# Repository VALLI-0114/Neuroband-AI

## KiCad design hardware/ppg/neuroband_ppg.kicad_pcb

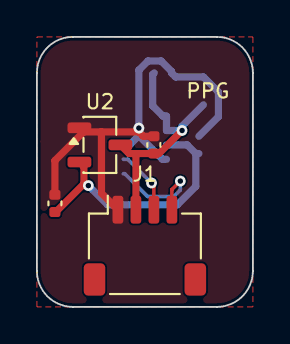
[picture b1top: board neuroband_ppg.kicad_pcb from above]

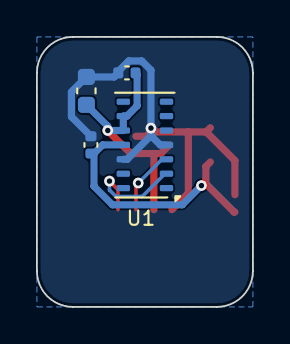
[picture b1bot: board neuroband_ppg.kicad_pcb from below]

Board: 2 copper layers, 12.0 x 15.0 mm, 8 parts (4 on the bottom side), 5 nets.

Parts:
C1, C2: 1uF; C_0402_1005Metric
C3, C5: 100nF; C_0402_1005Metric
C4: 10uF; C_0603_1608Metric
J1: MAIN; JST_SH_SM04B-SRSS-TB_1x04-1MP_P1.00mm_Horizontal
U1: MAX30102; Maxim_OLGA-14_3.3x5.6mm_P0.8mm
U2: XC6206P182MR; SOT-23-3

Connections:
1V8: C2.1, C3.1, U1.11, U2.2
3V3: C1.1, C4.1, C5.1, J1.2, U1.9, U1.10, U2.3
GND: C1.2, C2.2, C3.2, C4.2, C5.2, J1.1, U1.4, U1.12, U2.1
I2C_SCL: J1.4, U1.2
I2C_SDA: J1.3, U1.3

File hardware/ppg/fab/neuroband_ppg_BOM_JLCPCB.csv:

Comment,Designator,Footprint,LCSC Part #
1uF X5R/X7R 0402,"C1,C2",C_0402_1005Metric,
100nF X5R/X7R 0402,"C3,C5",C_0402_1005Metric,
10uF X5R/X7R 0603,C4,C_0603_1608Metric,
SM04B-SRSS-TB,J1,JST_SH_SM04B-SRSS-TB_1x04-1MP_P1.00mm_Horizontal,
MAX30102EFD+T,U1,Maxim_OLGA-14_3.3x5.6mm_P0.8mm,
XC6206P182MR,U2,SOT-23-3,

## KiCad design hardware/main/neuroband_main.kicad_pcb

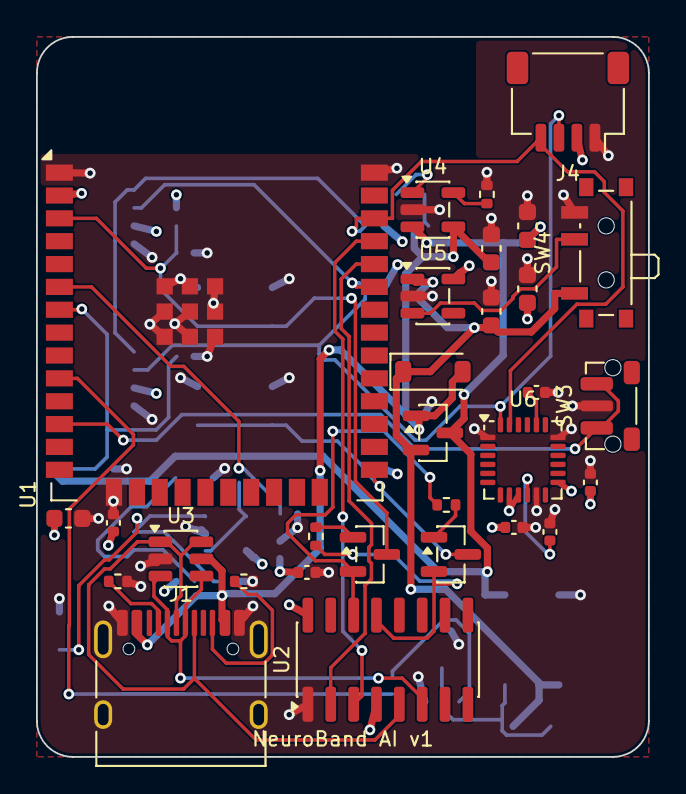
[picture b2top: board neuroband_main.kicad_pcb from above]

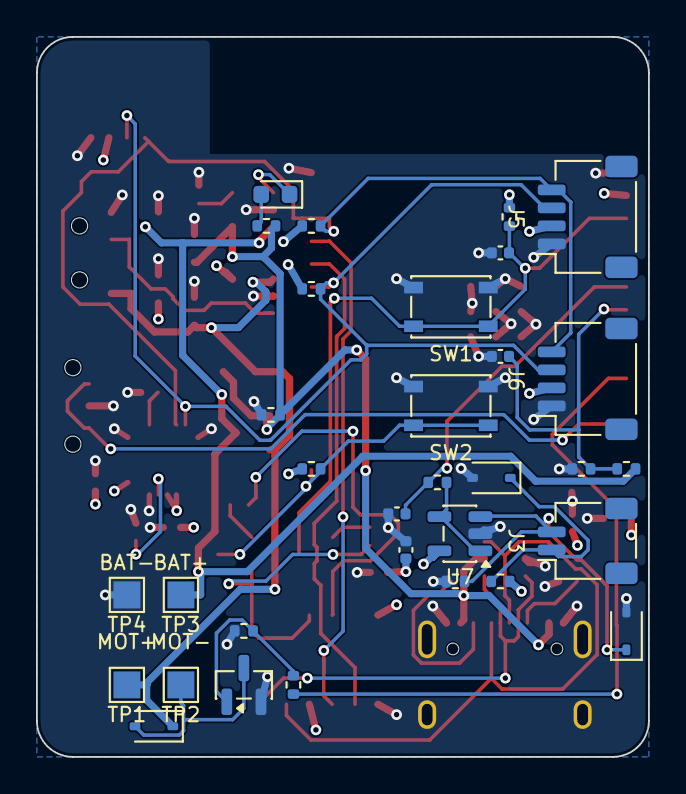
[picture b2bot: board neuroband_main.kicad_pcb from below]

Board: 4 copper layers, 34.0 x 40.0 mm, 62 parts (32 on the bottom side), 34 nets.

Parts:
C1, C16: 1uF; C_0402_1005Metric
C2, C7, C8: 10uF; C_0603_1608Metric
C3, C4, C10, C11, C13, C15: 100nF; C_0402_1005Metric
C5, C6: 4.7uF; C_0603_1608Metric
C12: 10nF; C_0402_1005Metric
C14: 2.2nF; C_0402_1005Metric
D1: B5819W; D_SOD-123
D2: 1N4148WS; D_SOD-323
D3, D4: PESD5V0S1BL; D_SOD-323
J1: USB-C; USB_C_Receptacle_HRO_TYPE-C-31-M-12
J3: GSR; JST_SH_SM02B-SRSS-TB_1x02-1MP_P1.00mm_Horizontal
J4: OLED; JST_SH_SM04B-SRSS-TB_1x04-1MP_P1.00mm_Horizontal
J5: PPG; JST_SH_SM04B-SRSS-TB_1x04-1MP_P1.00mm_Horizontal
J6: TEMP; JST_SH_SM04B-SRSS-TB_1x04-1MP_P1.00mm_Horizontal
LED1: CHG; LED_0603_1608Metric
Q1, Q2: MMBT3904; SOT-23
Q3: AO3401A; SOT-23
Q4: AO3400A; SOT-23
R1, R2, R3, R4, R15, R17: 10k; R_0402_1005Metric
R5, R6: 5.1k; R_0402_1005Metric
R7: 6.8k; R_0402_1005Metric
R8: 1k; R_0402_1005Metric
R9, R10, R11, R16, R19: 100k; R_0402_1005Metric
R13, R14: 4.7k; R_0402_1005Metric
R18: 100; R_0402_1005Metric
SW1: RESET; SW_SPST_PTS810
SW2: BOOT; SW_SPST_PTS810
SW3: BTN; SW_Push_1P1T-MP_NO_Horizontal_Alps_SKRTLAE010
SW4: POWER; SW_SPDT_PCM12
TP1: MOT+; TestPoint_Pad_1.5x1.5mm
TP2: MOT-; TestPoint_Pad_1.5x1.5mm
TP3: BAT+; TestPoint_Pad_1.5x1.5mm
TP4: BAT-; TestPoint_Pad_1.5x1.5mm
U1: ESP32-WROOM-32E-N4; ESP32-WROOM-32E
U2: CH340C; SOIC-16_3.9x9.9mm_P1.27mm
U3: USBLC6-2SC6; SOT-23-6
U4: MCP73831; SOT-23-5
U5: AP2112K-3.3; SOT-23-5
U6: MPU-6050; InvenSense_QFN-24_4x4mm_P0.5mm
U7: MCP6001; SOT-23-5

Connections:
3V3: C2.1, C3.1, C4.1, C8.1, C11.1, C12.1, C15.1, J4.2, J5.2, J6.2, R1.2, R2.2, R13.2, R14.2, R15.1, U1.2, U2.4, U2.16, U5.5, U6.8, U6.9, U6.13, U7.5
BATT_ADC: C10.1, R10.2, R11.1, U1.7
BTN: SW3.1, U1.12
CC1: J1.A5, R5.1
CC2: J1.B5, R6.1
CHG_PROG: R7.1, U4.5
CHG_STAT: LED1.1, U4.1
DTR: Q2.2, R3.1, U2.13
EN: C1.1, Q1.3, R1.1, SW1.1, U1.3
ESP_RX: U1.34, U2.2
ESP_TX: U1.35, U2.3
GND: C1.2, C2.2, C3.2, C4.2, C5.2, C6.2, C7.2, C8.2, C10.2, C11.2, C12.2, C13.2, C14.2, C15.2, C16.2, D3.2, D4.2, J1.A1, J1.A12, J1.B1, J1.B12, J1.SH, J4.1, J5.1, J6.1, Q4.2, R5.2, R6.2, R7.2, R9.2, R11.2, R16.2, R19.2, SW1.2, SW2.2, SW3.2, SW4.3, TP4.1, U1.1, U1.15, U1.38, U1.39, U2.1, U3.2, U4.2, U5.2, U6.1, U6.11, U6.18, U7.2
GSR_A: D3.1, J3.1, R15.2
GSR_ADC: C16.1, R17.2, U1.6
GSR_BUF: R17.1, U7.1, U7.4
GSR_X: D4.1, J3.2, R16.1, U7.3
I2C_SCL: J4.4, J5.4, J6.4, R14.1, U1.36, U6.23
I2C_SDA: J4.3, J5.3, J6.3, R13.1, U1.33, U6.24
IO0: Q2.3, R2.1, SW2.1, U1.25
LDO_EN: SW4.2, U5.3
LED_A: LED1.2, R8.2
MOTOR: R18.1, U1.10
MOTOR_G: Q4.1, R18.2, R19.1
MOTOR_N: D2.2, Q4.3, TP2.1
MPU_CP: C14.1, U6.20
MPU_REG: C13.1, U6.10
Q1_B: Q1.1, R3.2
Q2_B: Q2.1, R4.2
RTS: Q1.2, R4.1, U2.14
USB_DM: J1.A7, J1.B7, U2.6, U3.3, U3.4
USB_DP: J1.A6, J1.B6, U2.5, U3.1, U3.6
VBAT: C6.1, Q3.3, R10.1, TP3.1, U4.3
VBUS: C5.1, D1.2, J1.A4, J1.A9, J1.B4, J1.B9, Q3.1, R8.1, R9.1, U3.5, U4.4
VSYS: C7.1, D1.1, D2.1, Q3.2, SW4.1, TP1.1, U5.1

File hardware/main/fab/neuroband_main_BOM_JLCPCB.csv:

Comment,Designator,Footprint,LCSC Part #
1uF X5R/X7R 0402,"C1,C16",C_0402_1005Metric,
10nF X5R/X7R 0402,C12,C_0402_1005Metric,
2.2nF X5R/X7R 0402,C14,C_0402_1005Metric,
10uF X5R/X7R 0603,"C2,C7,C8",C_0603_1608Metric,
100nF X5R/X7R 0402,"C10,C11,C13,C15,C3,C4",C_0402_1005Metric,
4.7uF X5R/X7R 0603,"C5,C6",C_0603_1608Metric,
B5819W,D1,D_SOD-123,
1N4148WS,D2,D_SOD-323,
PESD5V0S1BL,"D3,D4",D_SOD-323,
TYPE-C-31-M-12,J1,USB_C_Receptacle_HRO_TYPE-C-31-M-12,
SM02B-SRSS-TB,J3,JST_SH_SM02B-SRSS-TB_1x02-1MP_P1.00mm_Horizontal,
SM04B-SRSS-TB,"J4,J5,J6",JST_SH_SM04B-SRSS-TB_1x04-1MP_P1.00mm_Horizontal,
Red LED 0603,LED1,LED_0603_1608Metric,
MMBT3904,"Q1,Q2",SOT-23,
AO3401A,Q3,SOT-23,
AO3400A,Q4,SOT-23,
10k 1% 0402,"R1,R15,R17,R2,R3,R4",R_0402_1005Metric,
4.7k 1% 0402,"R13,R14",R_0402_1005Metric,
100 1% 0402,R18,R_0402_1005Metric,
5.1k 1% 0402,"R5,R6",R_0402_1005Metric,
6.8k 1% 0402,R7,R_0402_1005Metric,
1k 1% 0402,R8,R_0402_1005Metric,
100k 1% 0402,"R10,R11,R16,R19,R9",R_0402_1005Metric,
PTS810 SJM 250 SMTR LFS,"SW1,SW2",SW_SPST_PTS810,
SKRTLAE010,SW3,SW_Push_1P1T-MP_NO_Horizontal_Alps_SKRTLAE010,
MSK-12C02 (PCM12 footprint),SW4,SW_SPDT_PCM12,
ESP32-WROOM-32E-N4,U1,ESP32-WROOM-32E,
CH340C,U2,SOIC-16_3.9x9.9mm_P1.27mm,
USBLC6-2SC6,U3,SOT-23-6,
MCP73831T-2ACI/OT,U4,SOT-23-5,
AP2112K-3.3TRG1,U5,SOT-23-5,
MPU-6050,U6,InvenSense_QFN-24_4x4mm_P0.5mm,
MCP6001T-I/OT,U7,SOT-23-5,

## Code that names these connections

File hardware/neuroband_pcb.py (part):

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SH4 = "Connector_JST:JST_SH_SM04B-SRSS-TB_1x04-1MP_P1.00mm_Horizontal"
SH2 = "Connector_JST:JST_SH_SM02B-SRSS-TB_1x02-1MP_P1.00mm_Horizontal"
TP = "TestPoint:TestPoint_Pad_1.5x1.5mm"
QWIIC = {"1": "GND", "2": "3V3", "3": "I2C_SDA", "4": "I2C_SCL"}  # Qwiic / STEMMA QT pin order


def R(v, a, b, **kw):
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                         "TXD": "ESP_RX", "RXD": "ESP_TX", "~{DTR}": "DTR", "~{RTS}": "RTS"}),
        "C4": C("100nF", "3V3", "GND", near="U2", pin="16"),
        "Q1": dict(sym="Transistor_BJT:MMBT3904", fp=SOT23, val="MMBT3904", mpn="MMBT3904",
                   conn={"B": "Q1_B", "E": "RTS", "C": "EN"}, near="U2", pin="14"),
        "Q2": dict(sym="Transistor_BJT:MMBT3904", fp=SOT23, val="MMBT3904", mpn="MMBT3904",
                   conn={"B": "Q2_B", "E": "DTR", "C": "IO0"}, near="U2", pin="13"),
        "R3": R("10k", "DTR", "Q1_B", near="Q1"),
        "R4": R("10k", "RTS", "Q2_B", near="Q2"),
        # --- battery, charger, power path, LDO, switch
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        "U4": dict(sym="Battery_Management:MCP73831-2-OT", fp=SOT235, val="MCP73831", mpn="MCP73831T-2ACI/OT",
                   at=(22.0, 9.6, 0),
                   conn={"V_{DD}": "VBUS", "V_{BAT}": "VBAT", "V_{SS}": "GND", "PROG": "CHG_PROG", "STAT": "CHG_STAT"}),
        "R7": R("6.8k", "CHG_PROG", "GND", near="U4", pin="5"),   # ~150 mA charge
        "C5": C("4.7uF", "VBUS", "GND", fp=C0603, near="U4", pin="4"),
        "C6": C("4.7uF", "VBAT", "GND", fp=C0603, near="U4", pin="3"),
        "R8": R("1k", "VBUS", "LED_A", near="LED1", side="B"),
        "LED1": dict(sym="Device:LED", fp="LED_SMD:LED_0603_1608Metric", val="CHG", mpn="Red LED 0603",
                     conn={"A": "LED_A", "K": "CHG_STAT"}, near="U4", pin="1", side="B"),
        "D1": dict(sym="Device:D_Schottky", fp="Diode_SMD:D_SOD-123", val="B5819W", mpn="B5819W",
                   conn={"A": "VBUS", "K": "VSYS"}, at=(22.0, 18.6, 0)),
        "Q3": dict(sym="Transistor_FET:AO3401A", fp=SOT23, val="AO3401A", mpn="AO3401A",
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        "R9": R("100k", "VBUS", "GND", near="Q3", pin="1", side="B"),
        "U5": dict(sym="Regulator_Linear:AP2112K-3.3", fp=SOT235, val="AP2112K-3.3", mpn="AP2112K-3.3TRG1",
                   at=(22.0, 14.4, 0), conn={"VIN": "VSYS", "GND": "GND", "EN": "LDO_EN", "VOUT": "3V3"}),
        "C7": C("10uF", "VSYS", "GND", fp=C0603, near="U5", pin="1"),
        "C8": C("10uF", "3V3", "GND", fp=C0603, near="U5", pin="5"),
        # slide switch: common (B) drives LDO EN, A = on (VSYS), C = off (GND); carries no load current
        "SW4": dict(sym="Switch:SW_SPDT", fp="Button_Switch_SMD:SW_SPDT_PCM12", val="POWER", mpn="MSK-12C02 (PCM12 footprint)",
                    conn={"A": "VSYS", "B": "LDO_EN", "C": "GND"}, at=(31.3, 12.0, 90)),
        "R10": R("100k", "VBAT", "BATT_ADC", near="U1", pin="7", side="B"),
        "R11": R("100k", "BATT_ADC", "GND", near="U1", pin="7", side="B"),
        "C10": C("100nF", "BATT_ADC", "GND", near="U1", pin="7", side="B"),
        # --- I2C bus + sensors
        "R13": R("4.7k", "I2C_SDA", "3V3", near="U1", pin="33", side="B"),
        "R14": R("4.7k", "I2C_SCL", "3V3", near="U1", pin="36", side="B"),
        "U6": dict(sym="Sensor_Motion:MPU-6050", fp="Sensor_Motion:InvenSense_QFN-24_4x4mm_P0.5mm", val="MPU-6050",
                   mpn="MPU-6050", at=(27.0, 23.5, 0),
                   # AD0 high -> I2C address 0x69 (firmware scans 0x68 and 0x69); it shares the VLOGIC pin next to it
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                         "REGOUT": "MPU_REG", "CPOUT": "MPU_CP", "SDA": "I2C_SDA", "SCL": "I2C_SCL"}),
        "C11": C("100nF", "3V3", "GND", near="U6", pin="13"),
        "C12": C("10nF", "3V3", "GND", near="U6", pin="8"),
        "C13": C("100nF", "MPU_REG", "GND", near="U6", pin="10"),
        "C14": C("2.2nF", "MPU_CP", "GND", near="U6", pin="20"),
        "J4": dict(sym="Connector_Generic:Conn_01x04", fp=SH4, val="OLED", mpn="SM04B-SRSS-TB", conn=QWIIC,
                   at=(29.5, 3.6, 180)),
        "J5": dict(sym="Connector_Generic:Conn_01x04", fp=SH4, val="PPG", mpn="SM04B-SRSS-TB", conn=QWIIC,
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        # --- GSR front-end
        "J3": dict(sym="Connector_Generic:Conn_01x02", fp=SH2, val="GSR", mpn="SM02B-SRSS-TB",
                   conn={"1": "GSR_A", "2": "GSR_X"}, at=(3.4, 28.0, 90), side="B"),
        "R15": R("10k", "3V3", "GSR_A", near="J3", pin="1", side="B"),
        "D3": dict(sym="Device:D_TVS", fp="Diode_SMD:D_SOD-323", val="PESD5V0S1BL", mpn="PESD5V0S1BL",
                   conn={"1": "GSR_A", "2": "GND"}, near="J3", pin="1", side="B"),
        "D4": dict(sym="Device:D_TVS", fp="Diode_SMD:D_SOD-323", val="PESD5V0S1BL", mpn="PESD5V0S1BL",
                   conn={"1": "GSR_X", "2": "GND"}, near="J3", pin="2", side="B"),
        "R16": R("100k", "GSR_X", "GND", near="J3", pin="2", side="B"),
        "U7": dict(sym="Amplifier_Operational:MCP6001-OT", fp=SOT235, val="MCP6001", mpn="MCP6001T-I/OT",
                   conn={"+": "GSR_X", "-": "GSR_BUF", "1": "GSR_BUF", "V+": "3V3", "V-": "GND"},
                   at=(10.5, 27.6, 0), side="B"),
        "C15": C("100nF", "3V3", "GND", near="U7", pin="5", side="B"),
        "R17": R("10k", "GSR_BUF", "GSR_ADC", near="U7", pin="1", side="B"),
        "C16": C("1uF", "GSR_ADC", "GND", near="U7", pin="1", side="B"),
        # --- side button, vibration motor
        "SW3": dict(sym="Switch:SW_Push", fp="Button_Switch_SMD:SW_Push_1P1T-MP_NO_Horizontal_Alps_SKRTLAE010",
                    val="BTN", mpn="SKRTLAE010", conn={"1": "BTN", "2": "GND"}, at=(32.0, 20.5, 90)),
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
